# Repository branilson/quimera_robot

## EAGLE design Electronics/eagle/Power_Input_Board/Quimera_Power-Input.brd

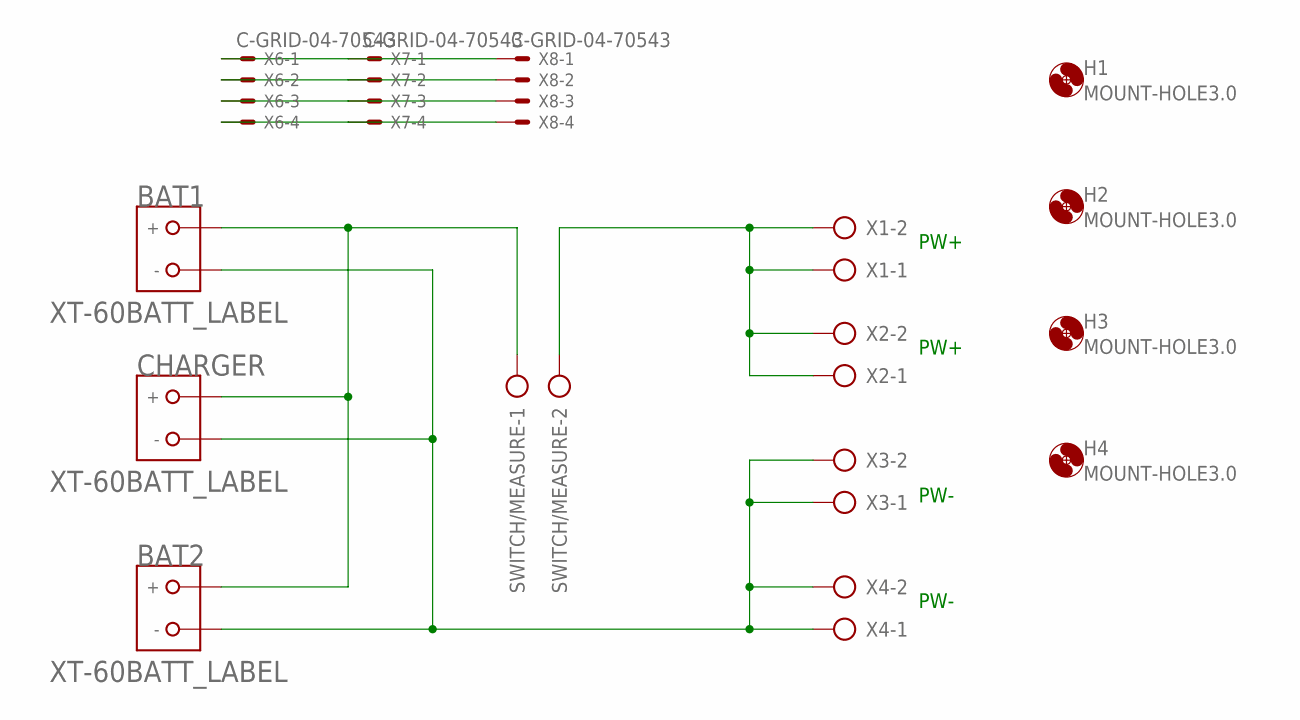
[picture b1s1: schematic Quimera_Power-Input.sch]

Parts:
BAT1, BAT2: XT-60BATT_LABEL; XT-60
CHARGER: XT-60BATT_LABEL; XT-60
H1, H2, H3, H4: MOUNT-HOLE3.0; 3,0
SWITCH/MEASURE: AK500/2
X1, X2, X3, X4: AK500/2
X6, X7, X8: C-GRID-04-70543; 70543-04

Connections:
unnamed: BAT1.GND (-), BAT2.GND (-), CHARGER.GND (-), X3.1, X3.2, X4.1, X4.2
unnamed: SWITCH/MEASURE.2, X1.1, X1.2, X2.1, X2.2
unnamed: BAT1.BATT (+), BAT2.BATT (+), CHARGER.BATT (+), SWITCH/MEASURE.1
unnamed: X6.1, X7.1, X8.1
unnamed: X6.2, X7.2, X8.2
unnamed: X6.3, X7.3, X8.3
unnamed: X6.4, X7.4, X8.4

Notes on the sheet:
PW-
PW+

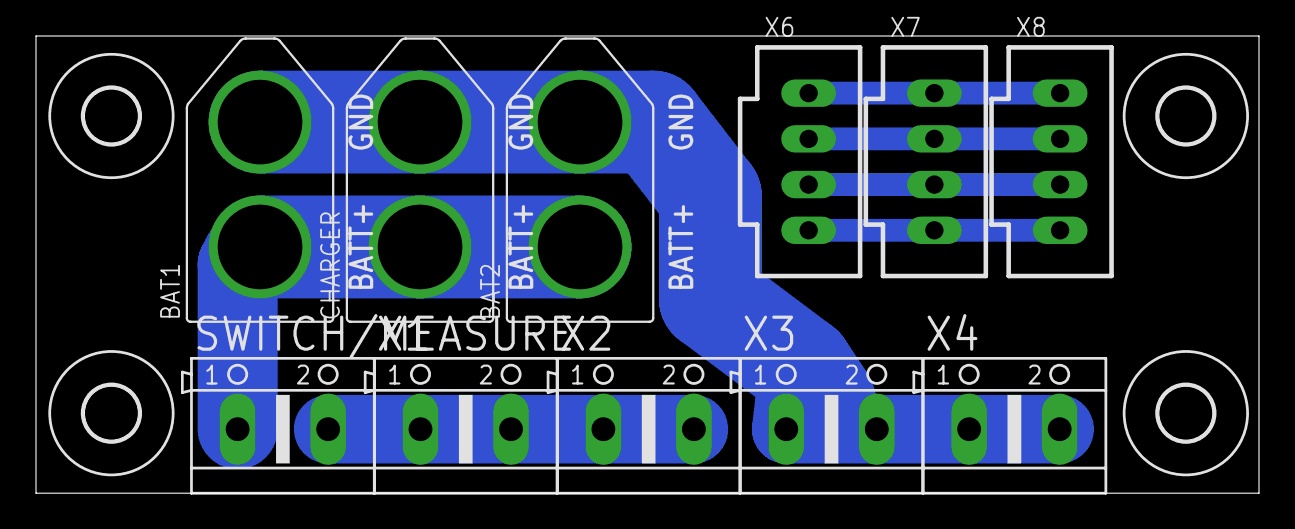
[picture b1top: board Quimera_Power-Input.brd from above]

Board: 2 copper layers, 67.9 x 25.4 mm, 15 parts (0 on the bottom side), 7 nets.

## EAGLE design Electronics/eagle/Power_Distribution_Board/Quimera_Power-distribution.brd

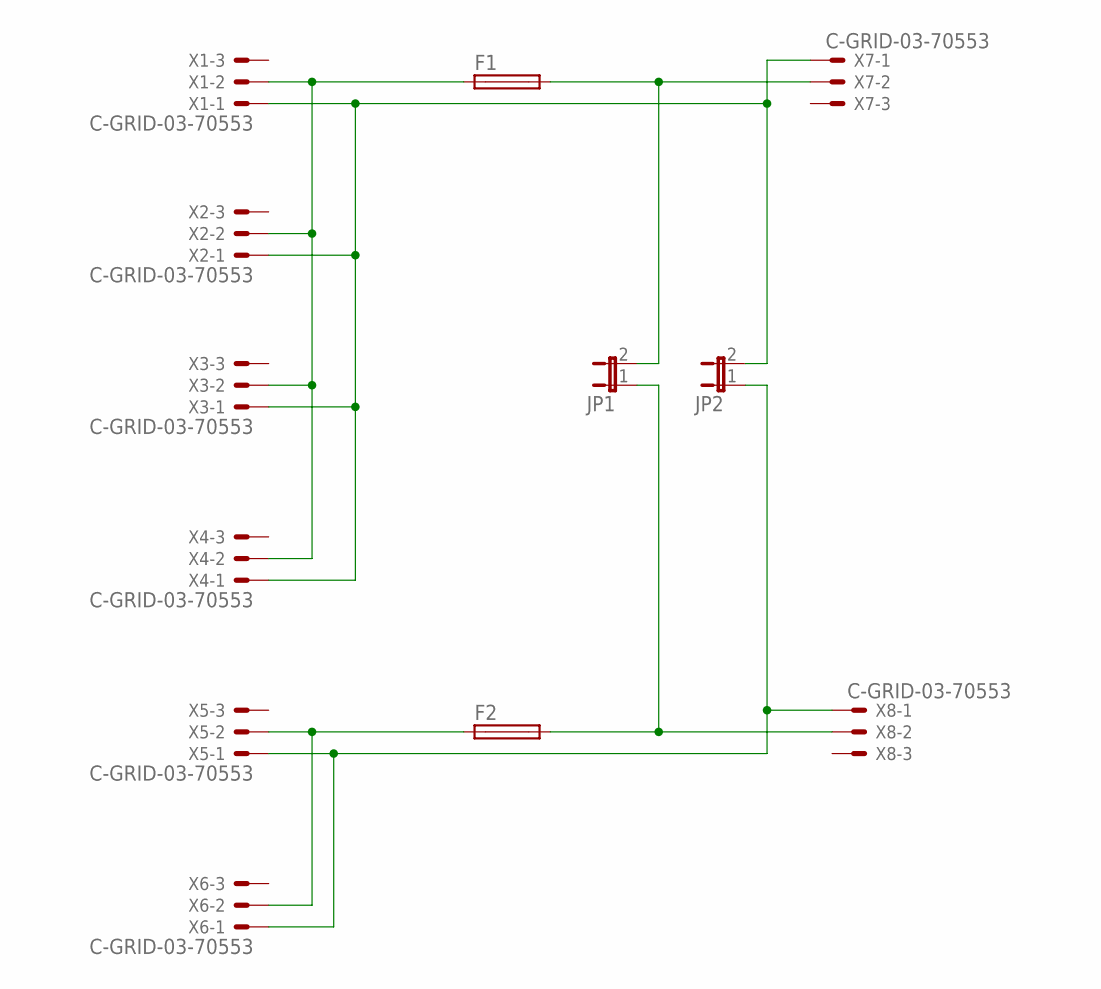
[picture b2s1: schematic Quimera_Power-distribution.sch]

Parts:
F1, F2: SH22,5A
JP1, JP2: JP1E; JP1
X1, X2, X3, X4, X5, X6, X7, X8: C-GRID-03-70553; 70553-03

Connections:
unnamed: F1.1, X1.2, X2.2, X3.2, X4.2
unnamed: F2.1, X5.2, X6.2
unnamed: F1.2, JP1.2, X7.2
unnamed: F2.2, JP1.1, X8.2
unnamed: JP2.2, X1.1, X2.1, X3.1, X4.1, X7.1
unnamed: JP2.1, X5.1, X6.1, X8.1

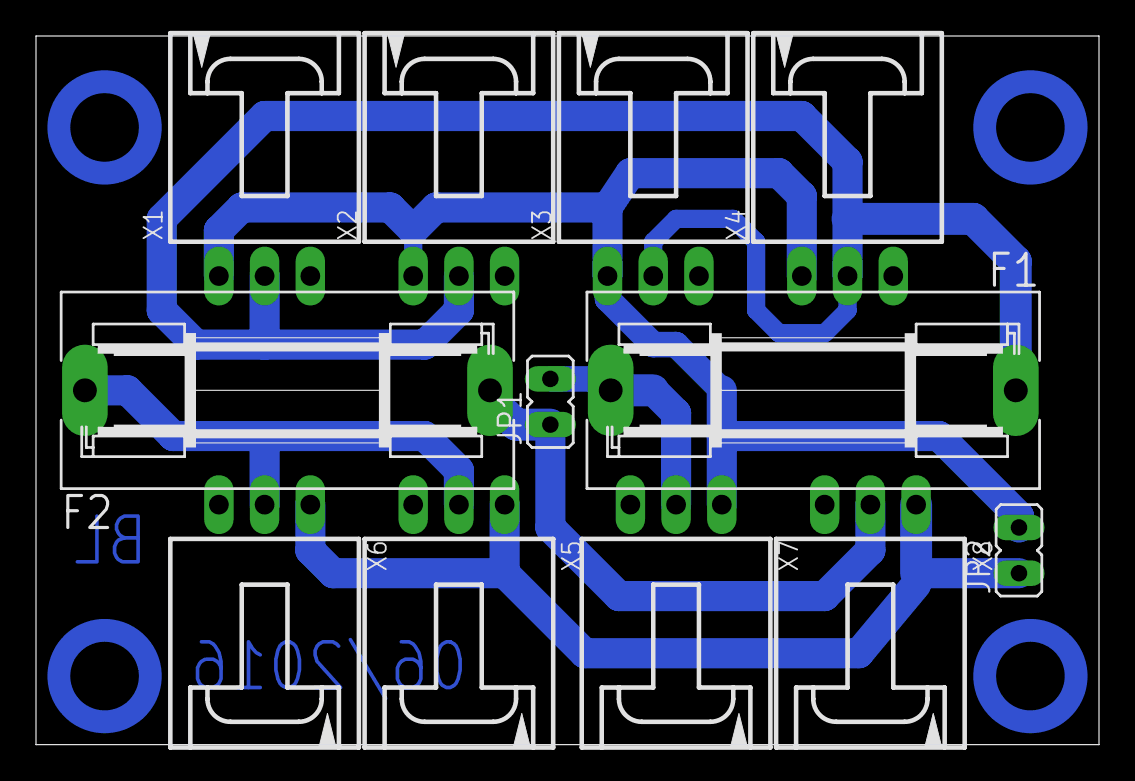
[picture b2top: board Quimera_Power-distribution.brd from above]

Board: 2 copper layers, 59.1 x 39.4 mm, 12 parts (0 on the bottom side), 6 nets.

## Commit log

2020-08-26 added_full_assembly
2020-09-02 Added electronic boards
2020-09-02 Finish mechanical assembly
2021-03-18 mod_add_lidar
2021-03-19 Change plates design
2021-04-04 add electrical diagram
2021-04-05 Added Eagle files
2021-04-07 Add IMU
2021-04-08 general updates
